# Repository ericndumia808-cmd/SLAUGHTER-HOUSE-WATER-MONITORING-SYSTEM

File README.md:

# SLAUGHTER-HOUSE-WATER-MONITORING-SYSTEM

# Collaborators
1. Masika Stephanie - Supervisor

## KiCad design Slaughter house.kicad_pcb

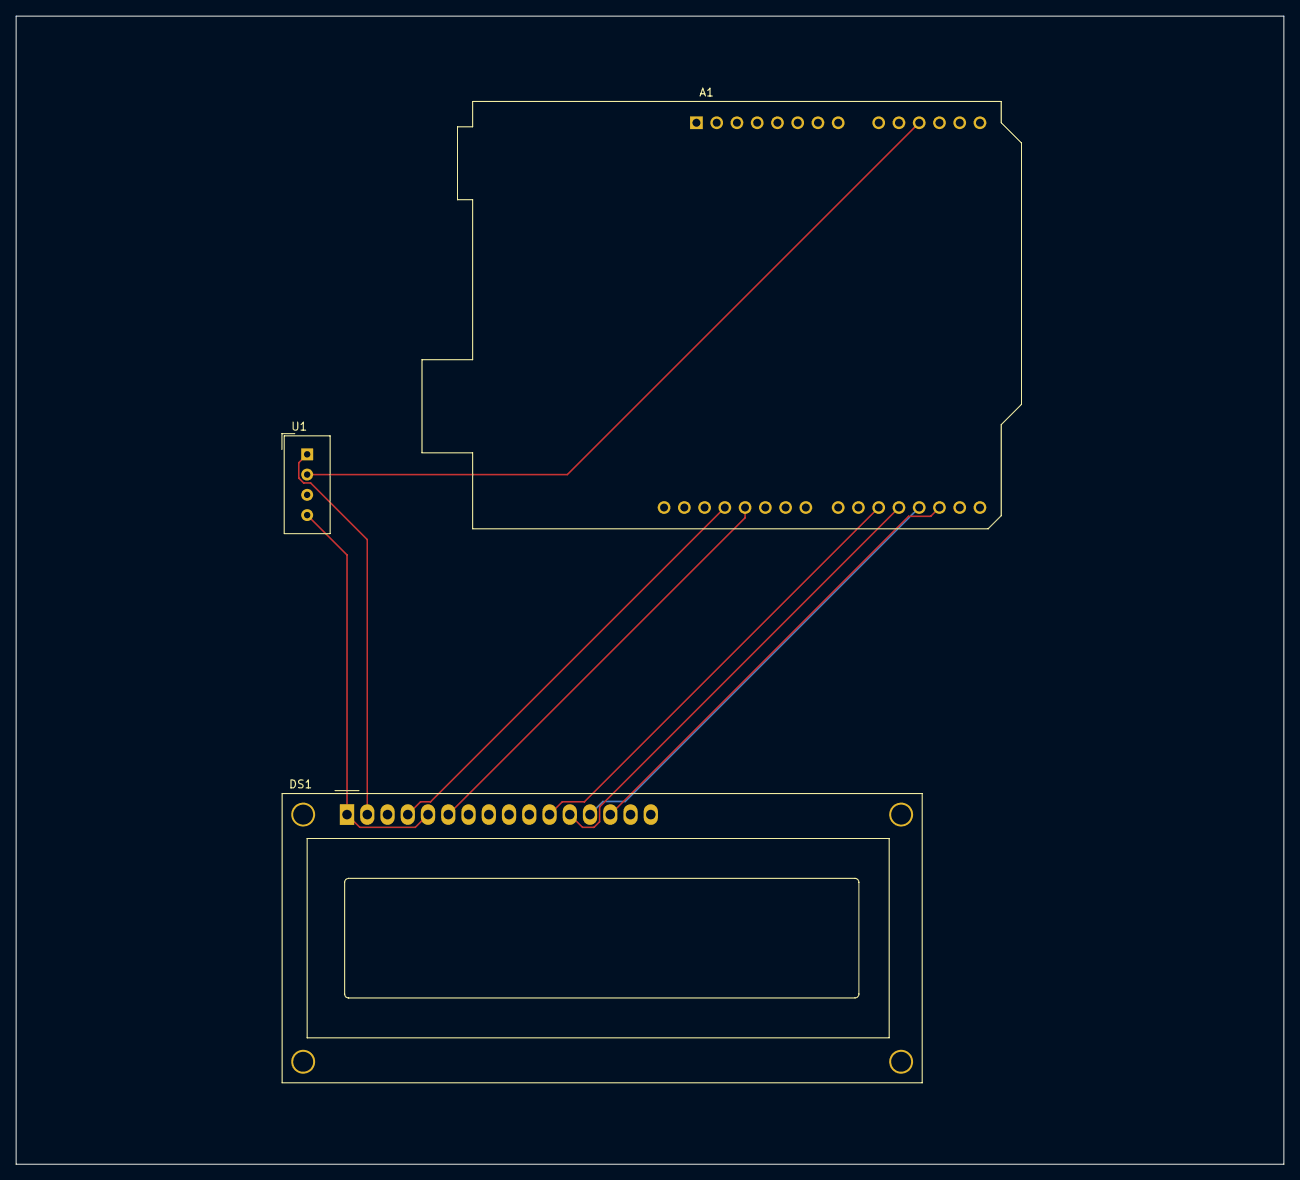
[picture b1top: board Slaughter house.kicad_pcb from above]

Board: 2 copper layers, 159.0 x 144.0 mm, 3 parts (0 on the bottom side), 9 nets.

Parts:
A1: Arduino_UNO_R2
DS1: WC1602A
U1: DHT11; Aosong_DHT11_5.5x12.0_P2.54mm

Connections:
+5V: DS1.2 (VDD), U1.1 (VDD)
GND: DS1.1 (VSS), DS1.5 (R/W), U1.4 (GND)
unnamed: A1.11 (A2), U1.2 (DATA)
unnamed: A1.17 (D2), DS1.14 (D7)
unnamed: A1.18 (D3), DS1.13 (D6)
unnamed: A1.19 (D4), DS1.12 (D5)
unnamed: A1.20 (D5), DS1.11 (D4)
unnamed: A1.26 (D11), DS1.6 (E)
unnamed: A1.27 (D12), DS1.4 (RS)
